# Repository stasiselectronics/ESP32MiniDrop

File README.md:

# ESP32MiniDrop
This repository contains the source files for a DIY Bluetooth connected solenoid controller for use with water drop photography. This project is still a work in progress, so make sure to follow and keep up with any future updates!

[Check out the project's companion page for even more details!](https://chandlermccowan.github.io/ESP32MiniDrop/)

## Quick Links
- [Board Schematics (download)](https://github.com/ChandlerMcCowan/ESP32MiniDrop/raw/master/Hardware%20Files/PDFs/ESP32MiniDrop_Schematics_A02.pdf)
- [Board Drawing (download)](https://github.com/ChandlerMcCowan/ESP32MiniDrop/raw/master/Hardware%20Files/PDFs/ESP32MiniDrop_Assembly_A02.pdf)
- [Enclosure Drawing (download)](https://github.com/ChandlerMcCowan/ESP32MiniDrop/raw/master/Enclosure%20Files/ESP32MiniDrop_Enclosure_Assembly_Drawing.pdf)

## Current Status

This project is still in its early stages, so this repository should be considered a work in progress. As of now, here is what has been done:
- Finalizing schematic and board design for revision A02
- First rounds of iterations on 3D printed parts for enclosure and solenoid stand
- Completed basic function testing for revision A01
- Test firmware developed for ESP32 to use Bluetooth serial communication to pass JSON objects for control and configuration

## Future Goals

Here's what needs to get done for this project:
- Develop firmware to enable connection to Android/iOS app
- Develop Android/iOS app
- Perform electrical tests on board design

## Usage
The goal for this device is to help make water drop photography a snap. Water drop photography focuses on macro shots of water or other liquids at various stages of impact. This controller enables you to use an electronically controlled valve (i.e. solenoid) positioned above a pool of liquid, where you can adjust the timing between succesive drops, the size of the drops themselves, and when to tell the camera to take the picture. By connecting your phone to the controller, you'll be able to dial in these settings and get significantly more repeatable shots than with manual methods.

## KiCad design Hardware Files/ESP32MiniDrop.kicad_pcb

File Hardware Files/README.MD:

# ESP32MiniDrop Hardware Files
Designed in KiCad 5.1.6 

This folder contains the source files for the PCB design of the ESP32MiniDrop, along with supporting documentation. Here you can find PDFs of the schematic, an assembly drawing, and gerbers used for fabrication. 

The board design is centered around the ESP32 WROOM 32D module. This has WiFi and Bluetooth included, which helps to reduce the auxillary components needed. The board has one screw terminal to attach bare wires to hook up the solenoid coil. The solenoid is controlled with a MOSFET with flyback diode attached. 

To help load Arduino sketches onto the board, an USB to UART IC is included in the design. This takes the USB data lines and converts them to the RS232 UART signals going to the ESP32. When programming, the script used to flash the chip will take advantage of the DTR and RTS signals to put the EPS32 into boot mode and automatically reset when done. 

**NOTE**
This board uses 0603 passive components and small outline packages, so a patient hand and good eyes (or a microscope) will be needed to hand solder. The CP2012N is in a Quad Flat no Lead (QFN) package, and is not an easy part to attach. You can skip the USB to UART chip and instead use the 0.100" programming headers (J5) to load the sketches on the ESP32 manually.

## Overview

## Bill of Materials
| Reference Designator          | Value              | Quantity | Manufacturer                        |         Part Number |
|-------------------------------|--------------------|:--------:|-------------------------------------|--------------------:|
| C1, C3                        | 0.1uF 50V          |     2    | Yageo                               |   CC0603ZRY5V9BB104 |
| C2, C5, C7                    | 10uF 50V           |     3    | Samsung Electro-Mechanics           |     CL31A106MBHNNNE |
| C4 C6                         | 1nF 50V            |     2    | Yageo                               |   CC0603KRX7R9BB102 |
| C8                            | 1uF 50V            |     1    | Yageo                               |   CC0603KRX5R9BB105 |
| C9                            | 22uF 6.3V          |     1    | Samsung Electro-Mechanics           |     CL21A226MQQNNNE |
| D1, D6                        | 40V 2A             |     2    | ON Semiconductor                    |              SS24FL |
| D2                            | SP0502BAHT         |     1    | Littelfuse Inc.                     |         SP0502BAHTG |
| D3                            | GREEN 3.2V 20mA    |     1    | Wurth Elektronik                    |       150120GS75000 |
| D4                            | BLUE 3.2V 20mA     |     1    | Wurth Elektronik                    |       150120BS75000 |
| D5                            | 20V 1A             |     1    | ON Semiconductor                    |       MBR120VLSFT3G |
| D7                            | 600V 5A            |     1    | SMC Diode Solutions                 |            SD560BTR |
| J1                            | USB_B_Mini         |     1    | Molex                               |          1050170001 |
| J2                            | Barrel_Jack        |     1    | CUI Devices                         |             PJ-037A |
| J3                            | AudioJack          |     1    | Kycon, Inc.                         |            STX-3000 |
| J4                            | Solenoid Terminal  |     1    | Pheonix Contact                     |             1935161 |
| Q1 Q2                         | S8050              |     2    | ON Semiconductor                    |       MMBT2222ALT1G |
| Q3                            | NMOS 60V 46A       |     1    | ON Semiconductor                    |        NTD5865NLT4G |
| R1, R2, R6, R7, R10, R13, R16 | 10k 1% 0.1W        |     7    | Yageo                               |     RC0603FR-0710KL |
| R14, R15                      | 220R 1% 0.1W       |     2    | Yageo                               |    RC0603FR-07220RL |
| R3                            | 22.1K 1% 0.1W      |     1    | Yageo                               |    RC0603FR-0722K1L |
| R4                            | 47.5K 1% 0.1W      |     1    | Yageo                               |    RC0603FR-0747K5L |
| R5                            | 2K 1% 0.1W         |     1    | Yageo                               |      RC0603FR-072KL |
| R8, R9, R11, R12              | 0R 0.1W            |     4    | Yageo                               |      311-0.0GRCT-ND |
| SW1                           | SPST (RED)         |     1    | TE Connectivity ALCOSWITCH Switches |           1825027-6 |
| SW2                           | SPST (BLUE)        |     1    | TE Connectivity ALCOSWITCH Switches |           1825027-8 |
| U1                            | CP2102N-A01-GQFN28 |     1    | Silicon Labs                        | CP2102N-A02-GQFN28R |
| U2                            | AZ1117-3.3         |     1    | Diodes Incorporated                 |    AZ1117CH-3.3TRG1 |
| U3                            | ESP32-WROOM-32     |     1    | Espressif                           |     ESP32-WROOM-32D |
| U4, U5                        | 4N25               |     2    | Broadcom Limited                    |           4N25-500E |

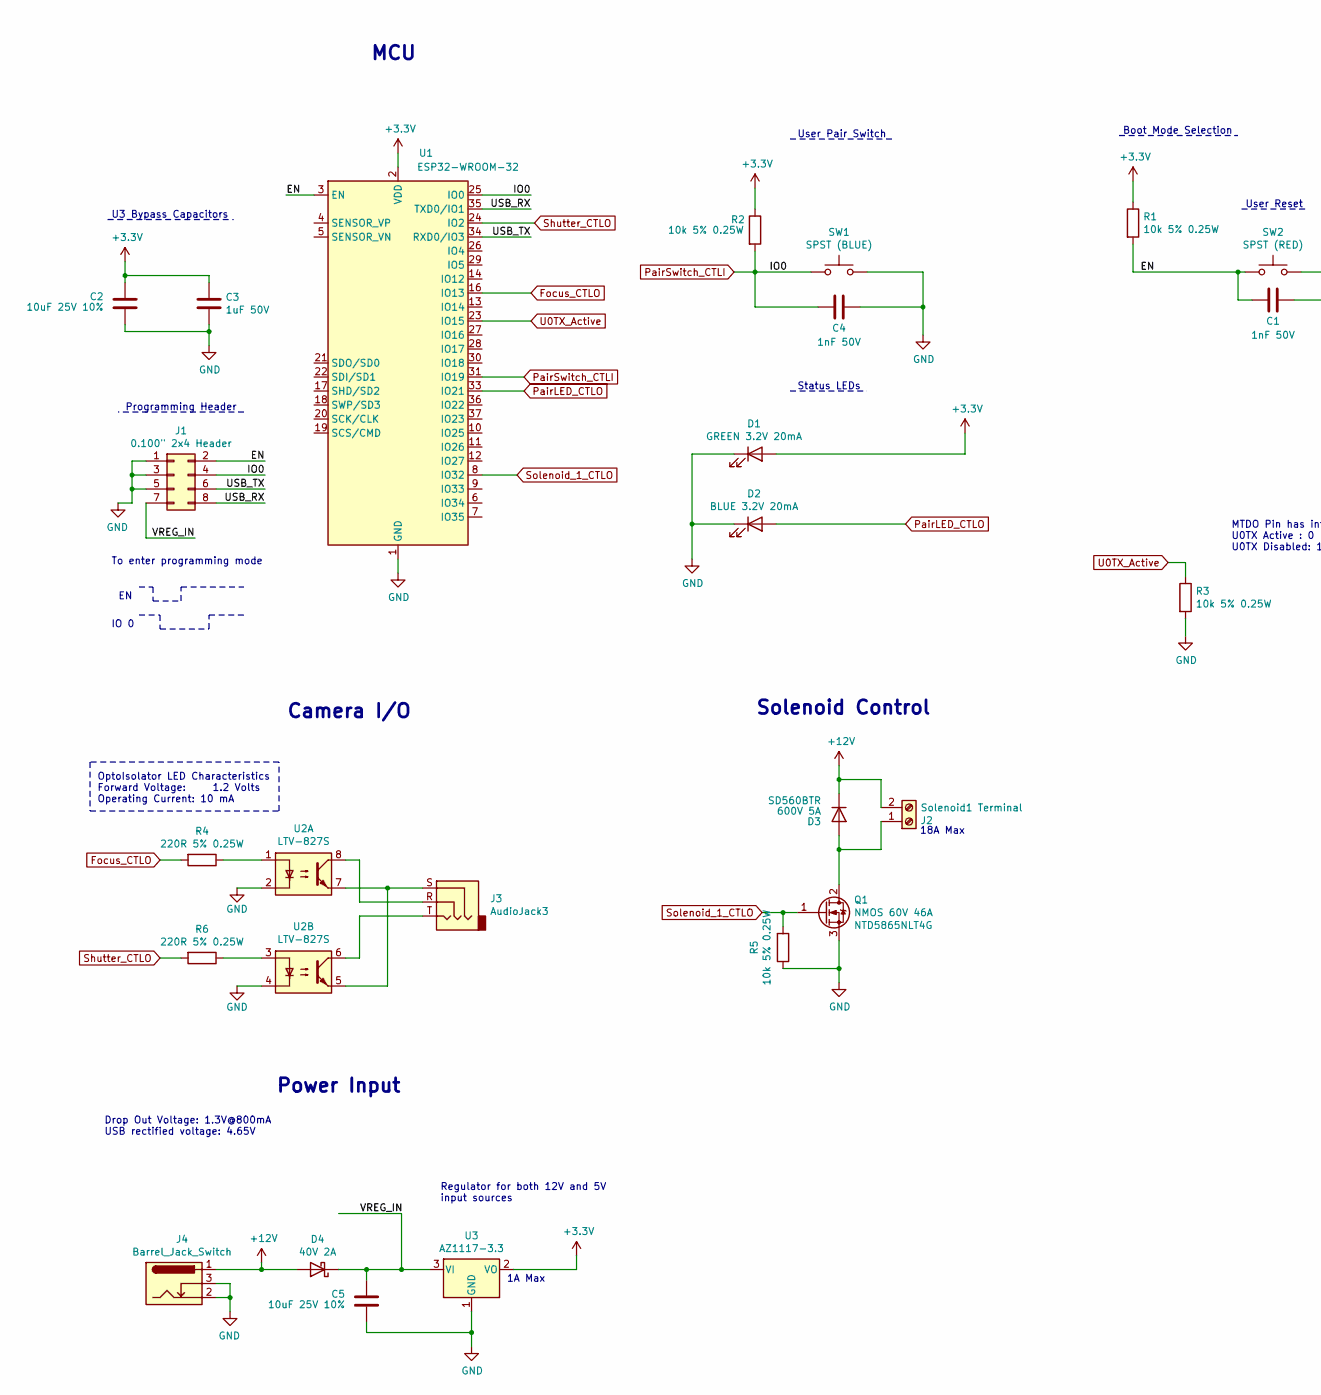
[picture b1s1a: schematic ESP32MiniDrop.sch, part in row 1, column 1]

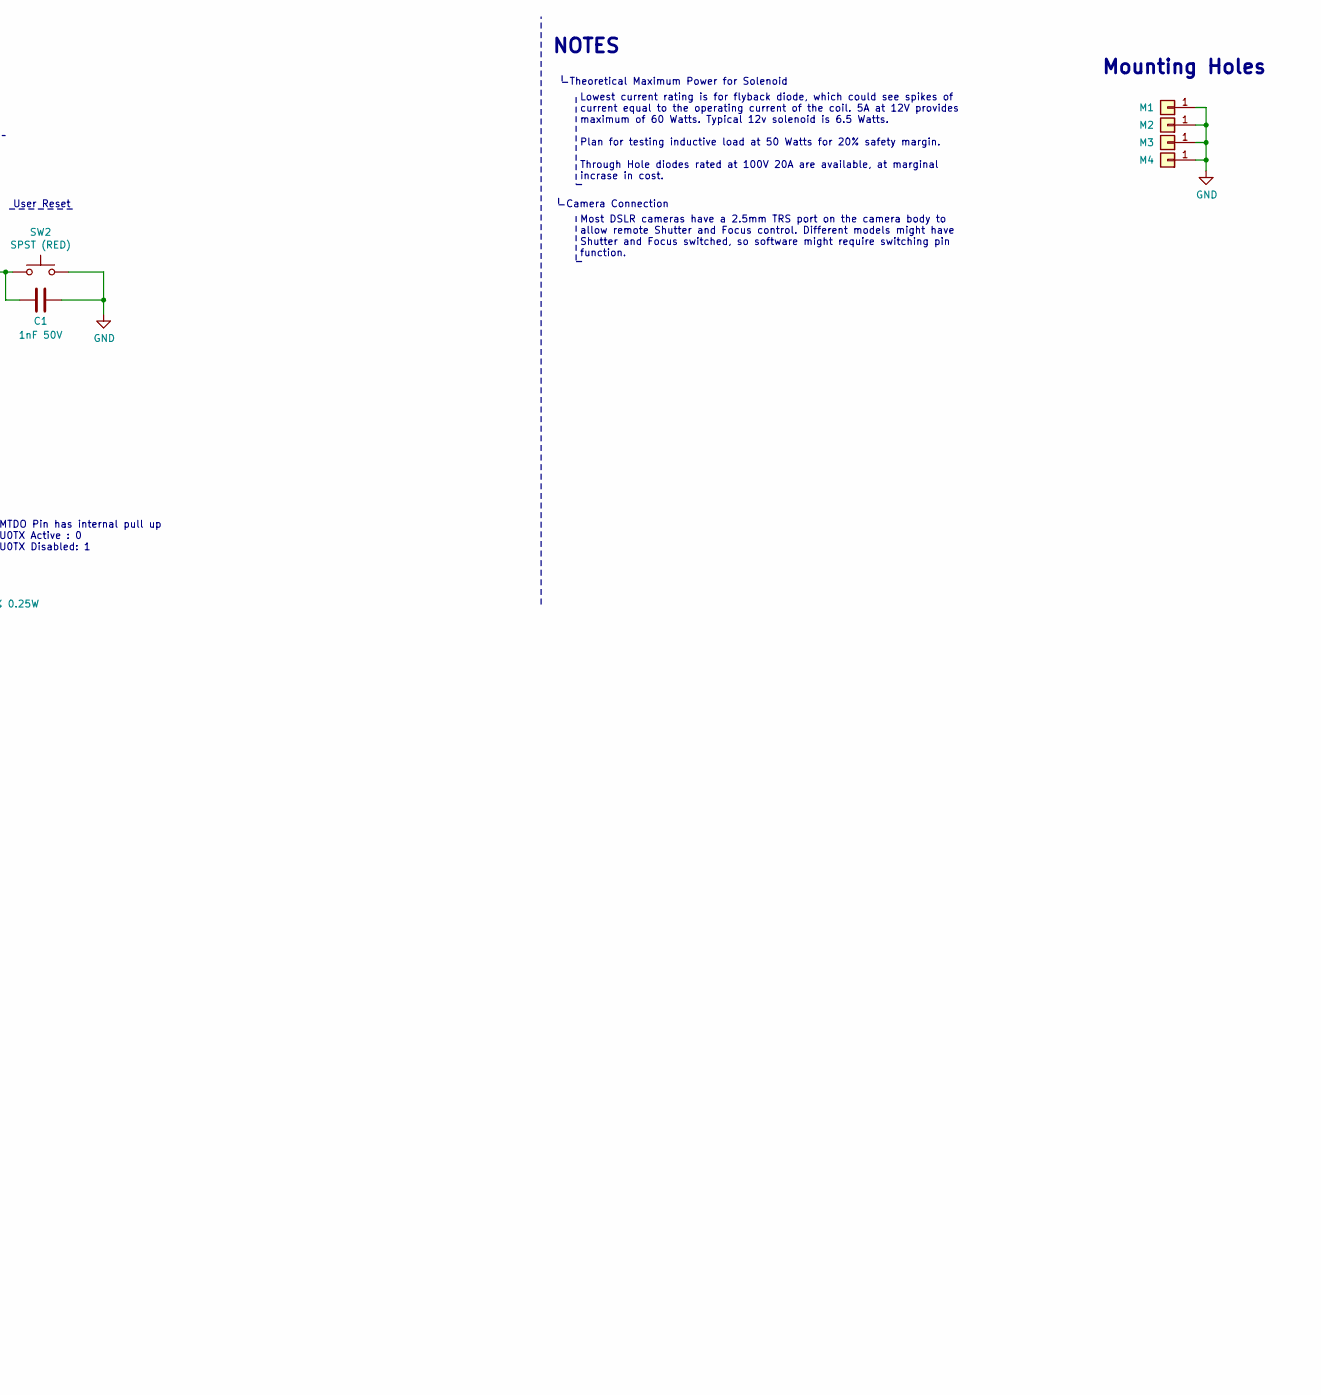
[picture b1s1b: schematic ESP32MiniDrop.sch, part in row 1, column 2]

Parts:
C1, C4: 1nF 50V; C_1206_3216Metric_Pad1.42x1.75mm_HandSolder; MPN 1206B102K500CT
C2, C5: 10uF 25V 10%; C_1206_3216Metric_Pad1.42x1.75mm_HandSolder; MPN CL31A106MAHNNNE
C3: 1uF 50V; C_1206_3216Metric_Pad1.42x1.75mm_HandSolder; MPN CL31B105KBHNFNE
D1: GREEN 3.2V 20mA; LED_1206_3216Metric_Pad1.42x1.75mm_HandSolder; MPN 150120GS75000
D2: BLUE 3.2V 20mA; LED_1206_3216Metric_Pad1.42x1.75mm_HandSolder; MPN 150120BS75000
D3: 600V 5A; D_SMB_Handsoldering; MPN SD560BTR
D4: 40V 2A; D_SOD-123F; MPN SS24FL
J1: 0.100\" 2x4 Header; PinHeader_2x04_P2.54mm_Vertical
J2: Solenoid1 Terminal; 1935161; MPN 1935161
J3: AudioJack3; SJ1-3523N; MPN SJ1-3523N
J4: Barrel_Jack_Switch; BarrelJack_Wuerth_6941xx301002_3D
M1, M2, M3, M4: Conn_01x01; MountingHole_3.2mm_M3_ISO7380_Pad
Q1: NMOS 60V 46A; TO-252-3_TabPin2; MPN NTD5865NLT4G
R1, R2, R3, R5: 10k 5% 0.25W; R_1206_3216Metric_Pad1.42x1.75mm_HandSolder; MPN RC1206JR-0710KL
R4, R6: 220R 5% 0.25W; R_1206_3216Metric_Pad1.42x1.75mm_HandSolder; MPN RC1206JR-07220RL
SW1: SPST (BLUE); 1825027-8; MPN 1825027-8
SW2: SPST (RED); 1825027-8; MPN 1825027-6
U1: ESP32-WROOM-32; MPN ESP32-WROOM-32D
U2: LTV-827S; SMDIP-8_W9.53mm
U3: AZ1117-3.3; SOT-223-3_TabPin2; MPN AZ1117CH-3.3TRG1

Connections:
+3V3: C2.2, C3.1, D1.2 (A), R1.1, R2.1, U1.2 (VDD), U3.2 (VO)
+12V: D3.1 (K), D4.2 (A), J2.2, J4.1
/EN: C1.2, J1.2, R1.2, SW2.1, U1.3 (EN)
/USB_RX: J1.8, U1.35 (TXD0/IO1)
/USB_TX: J1.6, U1.34 (RXD0/IO3)
/VREG_IN: C5.2, D4.1 (K), J1.7, U3.3 (VI)
Focus_CTLO: R4.2, U1.16 (IO13)
GND: C1.1, C2.1, C3.2, C4.1, C5.1, D1.1 (K), D2.1 (K), J1.1, J1.3, J1.5, J4.2, J4.3, M1.1, M2.1, M3.1, M4.1, Q1.3 (S), R3.2, R5.1, SW1.2, SW2.2, U1.1 (GND), U1.15 (GND), U1.38 (GND), U1.39 (GND), U2.2, U2.4, U3.1 (GND)
unnamed: D3.2 (A), J2.1, Q1.2 (D)
unnamed: J3.R, U2.8
unnamed: J3.S, U2.5, U2.7
unnamed: J3.T, U2.6
unnamed: R4.1, U2.1
unnamed: R6.1, U2.3
PairLED_CTLO: D2.2 (A), U1.33 (IO21)
PairSwitch_CTLI: C4.2, J1.4, R2.2, SW1.1, U1.25 (IO0), U1.31 (IO19)
Shutter_CTLO: R6.2, U1.24 (IO2)
Solenoid_1_CTLO: Q1.1 (G), R5.2, U1.8 (IO32)
U0TX_Active: R3.1, U1.23 (IO15)

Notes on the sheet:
Regulator for both 12V and 5V input sources
Boot Mode Selection
User Reset
Drop Out Voltage: 1.3V@800mA USB rectified voltage: 4.65V
OptoIsolator LED Characteristics Forward Voltage: 1.2 Volts Operating Current: 10 mA
U3 Bypass Capacitors
Status LEDs
User Pair Switch
Power Input
Camera I/O
Solenoid Control
Programming Header
MCU
NOTES
Theoretical Maximum Power for Solenoid
18A Max
Lowest current rating is for flyback diode, which could see spikes of current equal to the operating current of the coil. 5A at 12V provides maximum of 60 Watts. Typical 12v solenoid is 6.5 Watts. Plan for testing inductive load at 50 Watts for 20% safety margin. Through Hole diodes rated at 100V 2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
Camera Connection
Most DSLR cameras have a 2.5mm TRS port on the camera body to allow remote Shutter and Focus control. Different models might have Shutter and Focus switched, so software might require switching pin function.
IO 0
To enter programming mode
1A Max
Mounting Holes
MTDO Pin has internal pull up U0TX Active : 0 U0TX Disabled: 1

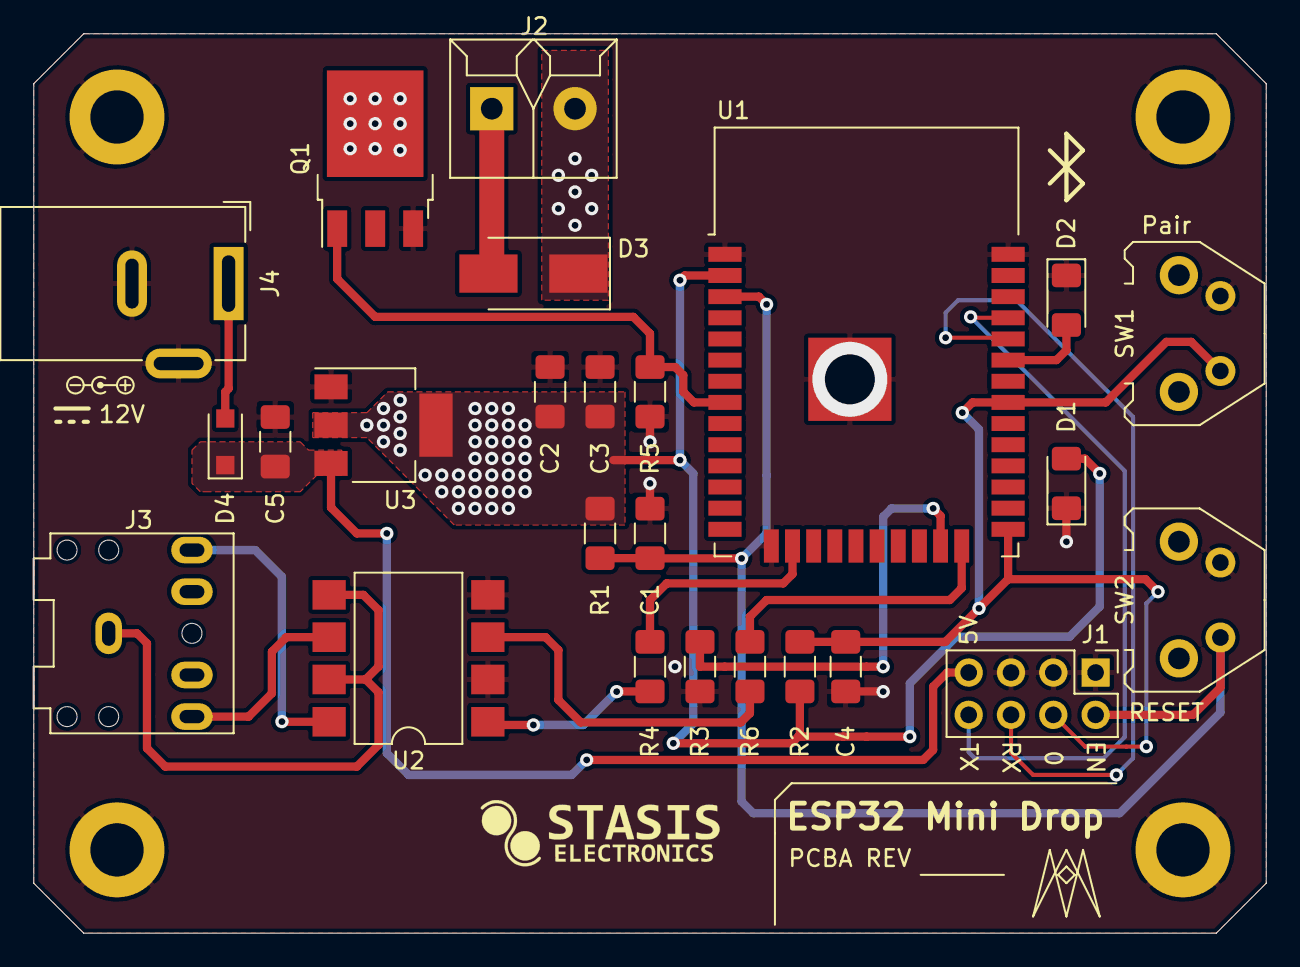
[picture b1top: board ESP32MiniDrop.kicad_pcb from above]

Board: 2 copper layers, 74.0 x 54.0 mm, 29 parts (0 on the bottom side), 19 nets.

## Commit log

2020-08-23 Updated FAB Files
2020-08-23 Added B.SilkS layer to output
2020-08-23 Fixed Missing References on PCB
2020-08-23 Updated Gerber Settings
2020-08-23 added 3d model
2020-08-25 Add missing silkskreen gerber
2020-08-25 Moved gitignore file
2020-08-25 Remove Ignored Files
2020-08-25 Cleanup Schematics
2020-08-25 Add Schematic PDF
2020-08-25 Add Assembly Files
2020-08-25 fixing
2020-08-25 Adding Assembly Files
2020-08-25 Add Assembly PNG
2020-08-25 Add Assembly PDF
2020-08-25 Update Assembly PNG
2020-08-25 Moving Step File
2020-08-25 Changed Programming Header to Virtual
2020-08-25 Add PCBA 3D Model
2020-08-25 Added Enclosure Top CAD File
2020-08-25 Updated Geometries
2020-08-25 Added Bottom Enclosure CAD File
2020-08-25 Geometry Updates
2020-08-25 Added STL Files
2020-08-25 Added Enclosure Images
2020-08-26 Add SVG files
2020-08-26 Set theme jekyll-theme-minimal
2020-08-26 Update Logo Files
2020-08-26 Add logo images
2020-08-26 Added Dimensions & Separate Pieces
2020-08-26 Added Dimensions and Title Block
2020-08-26 Add Assembly Drawing PDF
2020-08-26 Removed Files
2020-08-26 Update BOM
2020-08-26 Update wrong PN for Green LED
2020-08-26 Update Library
2020-08-26 Removed old library
2020-08-26 Moved Blank Page Template
2020-08-26 Removed old files
2020-08-26 Update project footprint library
2020-08-27 Change Schematics to Color
2020-08-27 Rename FAB folder to Fabrication Files
2020-08-27 update skin and info
2020-08-27 update photo
2020-08-27 add docs page
2020-08-29 Remove old files
2020-08-29 Add from template
2020-08-29 Update config file
2020-08-29 Remove template posts
2020-08-29 add new post
2020-08-29 update front page
2020-08-29 add images
2020-08-29 remove redundant files
2020-08-29 updates to docs
2020-08-29 add underscore directories
2020-08-29 go back to no underscores, whoops
2020-08-29 fix missing {{site.baseurl}}
2020-08-29 update images
2020-08-29 update wording
2020-08-29 add logo
2020-08-29 final updates for the night, man it is late
2020-08-30 missing docs
2020-08-30 fix links
2020-08-30 remove content
2020-08-30 update image
2020-08-30 update content
2020-08-30 remove icon on title
2020-08-30 update silkscreen color to black
2020-08-30 add image
2020-08-30 update assembly page
2020-08-30 fix link
2020-08-31 add Stand source files
2020-09-01 add post
2020-09-01 move files
2020-09-01 rename
2020-09-01 update post
2020-09-01 update schematics page
2020-09-01 fix image url
2020-09-01 Add post 2020-09-01-DesigningAStand.md
2020-09-01 update stand files and readme
2020-09-01 documentation updates
2020-09-01 Update Solenoid Bracket Geometry
2020-09-01 Add Rod Clip and Rod End
2020-09-02 Add Snap version of Solenoid Bracket
2020-09-02 Add stl file SolenoidBrackSnap
2020-09-02 update quickstart
2020-09-03 remove standard post
2020-09-03 add new blog post
2020-09-03 Add test firmware
2020-09-03 add beginning of parsing
2020-09-04 added Json parsing
2020-09-04 Update Geometry
2020-09-04 Clean up & connected LED
2020-09-04 Reduce Size
2020-09-04 Update Geometries
2020-09-04 add holding solenoid function
2020-09-04 add image to layout
2020-09-05 Add polygon pour to VREG IN
2020-09-05 Update RodEnd Geometry
2020-09-05 Add blue LED function
2020-09-05 fix shutter control hookup
2020-09-06 Switch Shutter & Focus (for canon)
2020-09-06 Add A01 build post
2020-09-07 update wordings and image urls
2020-09-07 reduce wordiness
2020-09-07 Fix pin mapping error on Q1, Q2
2020-09-07 add new post - fixing autodownload
2020-09-07 Fix transistor Q3 gate connection
2020-09-08 change solenoid control to pin 8 GPIO32
2020-09-08 Change mounting holes to M3, update tracks, change solenoid control to pin 8 of ESP32
2020-09-09 Add Solenoid Nozzle
2020-09-09 update Solenoid Bracket CAD file
2020-09-09 Add Solenoid Nozzle STL
2020-09-09 Update Solenoid Bracket STL
2020-09-09 Increase nut clearance
2020-09-09 Update Top Tripod Bracket geometry
2020-09-09 Update page on assembly
2020-09-10 Add Solenoid links to docs page
2020-09-10 Add stand links to sidebar
2020-09-10 add stand pages
2020-09-10 Add stand components page
2020-09-19 fix Solenoid MOSFET Pin Mapping
2020-09-19 section off Do Not Place parts
2020-09-20 Remove USB to UART components
2020-09-20 Unroute USB to UART components
2020-09-20 Update passives to all 1206, unroute and reposition
2020-09-20 Reroute components
2020-09-20 Attach Pair Switch to ESP32 IO0 for boot mode selection
2020-09-20 Update Component MPN and Values
2020-09-20 Change barrel jack part, update routing
2020-09-20 Update Gerbers
2020-09-21 Add 3D models
2020-09-21 Change Audio Jack to SJ1-3523N
2020-09-21 Update 3.3V trace routing
2020-09-21 Change libraries to relative project library
2020-09-21 Update library paths
2020-09-26 Refresh Gerbers
2020-09-26 Fix missing library item
2020-09-27 Add missing post
2020-09-30 Add logo and update PCBA Rev
2020-10-03 Update Pages
